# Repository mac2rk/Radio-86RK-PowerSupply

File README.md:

# USB powered Radio-86RK (even from a power bank!)

Compact DC/DC converter to power i8080 and other vintage NMOS ICs from USB.

Intel i8080 CPU, MK4116 DRAM, NTE2708 EPROM and similar NMOS ICs from 1970s require three power supply voltages: +12V, -5V and +5V.

This project is a compact DC/DC converter that converts +5V from USB connector to +12V and -5V. This allows powering a retro computer, such as the [Radio-86RK](https://github.com/mac2rk/Radio-86RK-SRAM), from an inexpensive USB wall wart or from a portable battery ("power bank").

Note that some USB wall warts, even rated for high current, drop their output voltage from the nominal 5V to 4.5V and lower when delivering relatively modest 1A. Since +5V is not converted or regulated in any way, using such USB wall wart can affect the performance of the device being powered.

## Schematic and PCB Layout
[Schematic](Eagle/rk86-psu-sch.pdf)

[PCB Layout](Eagle/rk86-psu-pcb.pdf)

## Bill of Materials

Qty | Value   | Device    | Package   | Parts      | Description
--- | ------- | --------- | --------- | ---------- | -----------
1   | LMR62014XMF | IC    | SOT23-5   | U1         | LMR62014 SIMPLE SWITCHER® Step-Up Voltage Regulator 
1   | TC59ECB | IC        | SOT23-3   | U2         | Low Dropout, Negative Output Voltage Regulator                             
2   | MBR0520 | DIODE     | SOD123    | D1, D2     | Schottky diode                                                             
3   |         | LED       | 0805      | D3, D4, D5 |                                                                        
2   | 10u     | Inductor  | SRN6045TA | L1, L2     | Bourns SRN6045TA Series Semi-shielded Power Inductor                                                           
1   | 117k    | Resistor  | 0805      | R1         |
1   | 13.3k   | Resistor  | 0805      | R2         |
2   | 330 ohm | Resistor  | 0805      | R3, R4     |
1   | 1k      | Resistor  | 0805      | R5         |
3   | 2.2uF   | Capacitor | 1206      | C1, C5, C6 | Ceramic capacitor                                                                               
2   | 4.7u    | Capacitor | 1206      | C2, C4     | Ceramic capacitor
1   | 220pF   | Capacitor | 0805      | CF         | Ceramic capacitor                                                                              
1   | 1A      | PTC fuse  | 1812      | F1         |
1   |         | USB connector | Micro USB | USB1   | UJ2-MIBH2-4-SMT

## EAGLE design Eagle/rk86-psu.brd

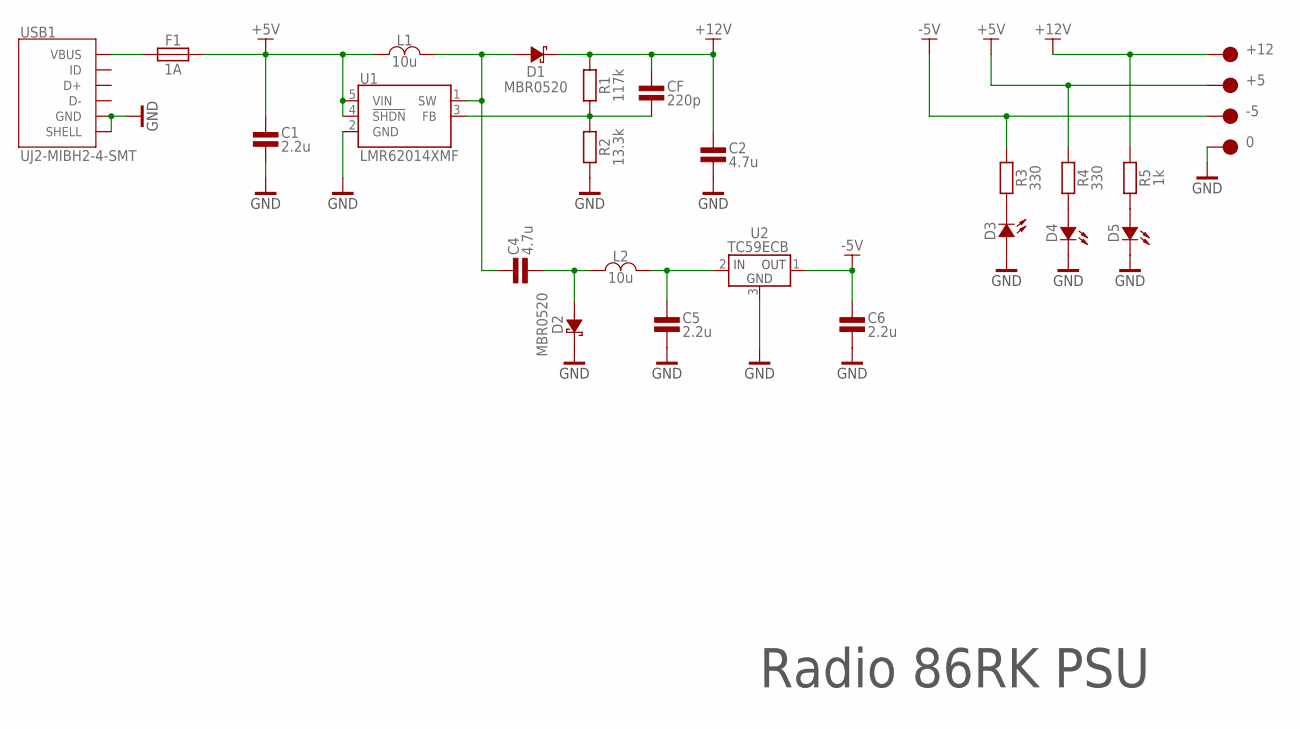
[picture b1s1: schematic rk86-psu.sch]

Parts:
0: WIREPAD_BOX
+5, +12: WIREPAD_BOX
-5: WIREPAD_BOX
C1, C5, C6: 2.2u; 1206
C2, C4: 4.7u; 1206
CF: 220p; 0805
D1, D2: MBR0520; SOD123
D3, D4, D5: LED0805; 0805POL
F1: 1A; 1812
L1, L2: 10u; BOUNRNS_SRN6045TA
R1: 117k; 0805
R2: 13.3k; 0805
R3, R4: 330; 0805
R5: 1k; 0805
U1: LMR62014XMF; SOT23-5
U2: TC59ECB; SOT23-3
USB1: UJ2-MIBH2-4-SMT

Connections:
+5V: +5.P$1, C1.2, F1.P$2, L1.P$1, R4.2, U1.4 (!SHDN), U1.5 (VIN)
+12V: +12.P$1, C2.2, CF.2, D1.K, R1.2, R5.2
-5V: -5.P$1, C6.2, R3.2, U2.1 (OUT)
GND: 0.P$1, C1.1, C2.1, C5.1, C6.1, D2.K, D3.A, D4.K, D5.K, R2.1, U1.2 (GND), U2.3 (GND), USB1.5 (GND), USB1.S1 (SHELL), USB1.S2 (SHELL), USB1.S3 (SHELL), USB1.S4 (SHELL), USB1.S5 (SHELL)
unnamed: CF.1, R1.1, R2.2, U1.3 (FB)
unnamed: C4.2, D1.A, L1.P$2, U1.1 (SW)
unnamed: C4.1, D2.A, L2.P$1
unnamed: C5.2, L2.P$2, U2.2 (IN)
unnamed: F1.P$1, USB1.1 (VBUS)
unnamed: D3.K, R3.1
unnamed: D4.A, R4.1
unnamed: D5.A, R5.1

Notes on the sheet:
Radio 86RK PSU

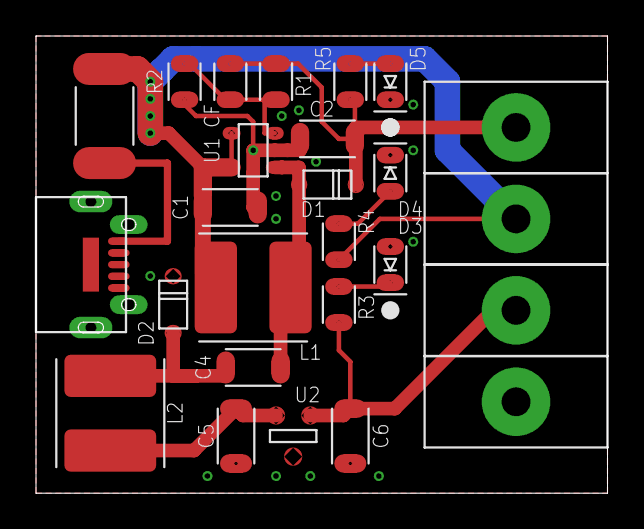
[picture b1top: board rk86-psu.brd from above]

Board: 2 copper layers, 31.7 x 25.4 mm, 26 parts (0 on the bottom side), 12 nets.
